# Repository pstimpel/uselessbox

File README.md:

# uselessbox
Just another useless box

3D printed useless box or so called useless machines. Arduino driven. Features 4 servos and a gesture/proximity sensor. Contains a 16 LED neopixel ring. All parts are easy to source. 

## Video in Action
https://www.youtube.com/watch?v=pDcApzEbbxg

## List of parts, sources (no affiliate links)
1x Arduino Nano V3 5V

1x Gesture/proximity sensor, 5V (!) similar to https://www.distrelec.de/de/naeherungs-licht-rgb-und-gestensensor-apds9960-5v-adafruit-3595/p/30139163

1x switch, similar to https://www.amazon.de/gp/product/B07MY2WVQ3/

1x jack similar to https://www.amazon.de/gp/product/B009PH1J5Y/

1x power adaptor similar to https://www.amazon.de/gp/product/B07HSPT57Y

4x servo motors, similar to https://www.amazon.de/gp/product/B06XQD18QN

cables, solder stuff

22x M3*10 scews

5x M3*8 screws

2x M3*20 screws

1x Neopixel 16 LED ring similar to https://www.distrelec.de/de/neopixel-ring-mit-16-rgb-leds-adafruit-1463-neopixel/p/30091142

1x resistor 1/4W 260 Ohm

1x resistor 1/4W 10 kOhm

20x 2.54mm pin headers

2x 5mm 2pol screw terminals

some steering servo push wire, 0.6mm will do. You need about 10 cm.

some double sided tape

optional: stuff to create PCBs

## Instructions
Optional: create your PCB

Just 3d print the parts, each part one time. I printed the "OK fingers" in 0.1mm, and all other stuff in 0.25mm. I used cubic infill, 2 shells, and 3 shells on bottom and top. I did not use any support except for the LED housing. I was using PLA from https://dasfilament.de

Mount one servo to the back part. The axis on top is showing to the outside. Add the lid servo arm. Mount the lid to the back using M3*20 screws. Now use the steering servo push wire. Make sure your servo is at center position when doing that. Make the wire as long as you need it so the lid and back are located rectangular.

Mount the back to the bottom, using 4 M3*10 screws. 

Mount the usb door using the usb door frame, to the the front. Mount the front to the bottom using 4 M3*10 screws.

Mount the jack to the bottom rear and lock it using the "Buchsenhalter" (sorry, forgot to translate it) to the bottom. Use 2 M3*8 screws.

Solder 5 cables to the gesture sensor board, but do not use the pins for this breakout board. If you have, use some old servo cable or anything similar that would match to pins at your main board if you use any. If there are no pins, you will have to solder the wires to the main board later. Make the cables around 15cm long. Mount the sensor board to the top, using the Sensorlock and 2 M3*8 screws.

Solder 2 cables to your switch. Mount the switch to the top. The "on position" of the switch has to show away from the sensor board. Make these cables around 15cm long.

Solder 3 more cables to your neopixel ring (ground, V+, data in). Make these cables 15 cm long, and use again some old servo cables or other cables matching pins. Add the neopixel ring to the housing, and close it using the LED cover. Btw, print this in transparent filament, if you have. Nice light effects are waiting for you. Lock the housing and the cover by another M3*8 screw. The neopixel ring points towards the cover with its LEDs. Mount the LED housing on top of your top part, and lock it using some M3*10 screws. The LED point towards the front. Moint the "flag arm" to one servo, and this servo to the top part. If you look from behind, the axis points to you and to the left. You can add some white label to the flag holder, to create a small flag. Mount the top to the front using another 4 M3*10 screws.

Mount the finger to one servo, do not lock it up yet. Mount the servo to the right housing part, axis to the right. Mount the right housing to the already mounted parts, mount it on the right side when you look from behind! Use 5 M3*10 screws.

OK, we enter the finish line, slowly...

Mount the 4th servo to the "left" part. Axis point to the front, but downwards. Connect OK fingers and "assholearm" together using another M3*10 screw. Mount the whole arm to the servo. DO NOT CLOSE THE HOUSING YET!

Connect all wires (servos, LED, switch, jack, gesture sensor) to your PCB. Take care for not short cutting anything. Use double sided tape and mount your PCB in a way you can reach the USB of te arduino throught the "usb door" at the front of your housing. Make sure again you do not block any servo movement by cables.

It is time to connect the power adaptor. If nothing smokes, you got your solder job the right way.

Make sure the switch on top of your new toy is in Off position, pointing to the front. Connect USB and your PC. Fire up your Arduino IDE, load the sketch and push it to the Arduino. Maybe you need to activate libraries for servos, or FastLED or the gesture sensor. Just follow the instruction of these vendors.

After the reboot, the LED should light up in blue and kind of glow...if you put your finger on the sensor, it should glow red, brightness depending on how close your finger is to the sensor.

At the same time, all your servos were "reset". You can now tighten all the screws of the servo arms connecting to the servo heads.

Servo for Lid: in reset position the LID should be closed

Servo for Flag: in reset position the flag arm should be horizontal, but below the edge of the top.

Servo for OKFinger/Asshole: The door should be closed, the fingers hidden.

Servo for Finger: Tricky one. Push the switch backwards and watch your finger if it makes it way to the switch. Idealy, it should turn the switch off. Just adjust until this happens. Hint: give a little extra push, just about 2-3 mm. Finally, tighten the screw.

OK, if all mechanics are working as expected, your useless machine should work as expected. You can now close the housing, using the last 5 M3*10 screws.

## What does it do?
Basically, the Arduino will cycle trough different ways the servos work. To start the machine, just push the switch to on. The main task of this machine is to push the switch into its off position.

Step 1: open lid, push switch off

Step 2: open lid very harsh, push switch off. After that the lid will open depending on how close your finger is to the sensor.

Step 3: open lid again, push switch off

Step 4: open lid, waving white flag, close the lid. Open the lid, push off the switch, close the lid.

Step 5: show the OK finger / asshole finger (as you prefer), then open the lid, push the switch, close the lid.

Of course you are invited to extent the possible action, color codes and so on. Just make sure to not use "delay()" too heavy, since this will interrupt the glowing of the LED.

## Frequently asked questions
### Why do you enable and disable the servos that much?
I found my servos to be really cheap ones. They interfere with each other. Disabling the servos I do not need for the moment solved this. However, in the video you can see the servos "choking". If you can, buy quality servos.

## Credits
The "OK finger" was remixed out of https://www.thingiverse.com/thing:3370059 by tdkahn1978 .

## Crosslinks

Repo
https://github.com/pstimpel/uselessbox

Thingiverse
https://www.thingiverse.com/thing:3901482

Prusaprinters
https://www.prusaprinters.org/prints/6042-another-useless-box

Youtube
https://www.youtube.com/watch?v=pDcApzEbbxg

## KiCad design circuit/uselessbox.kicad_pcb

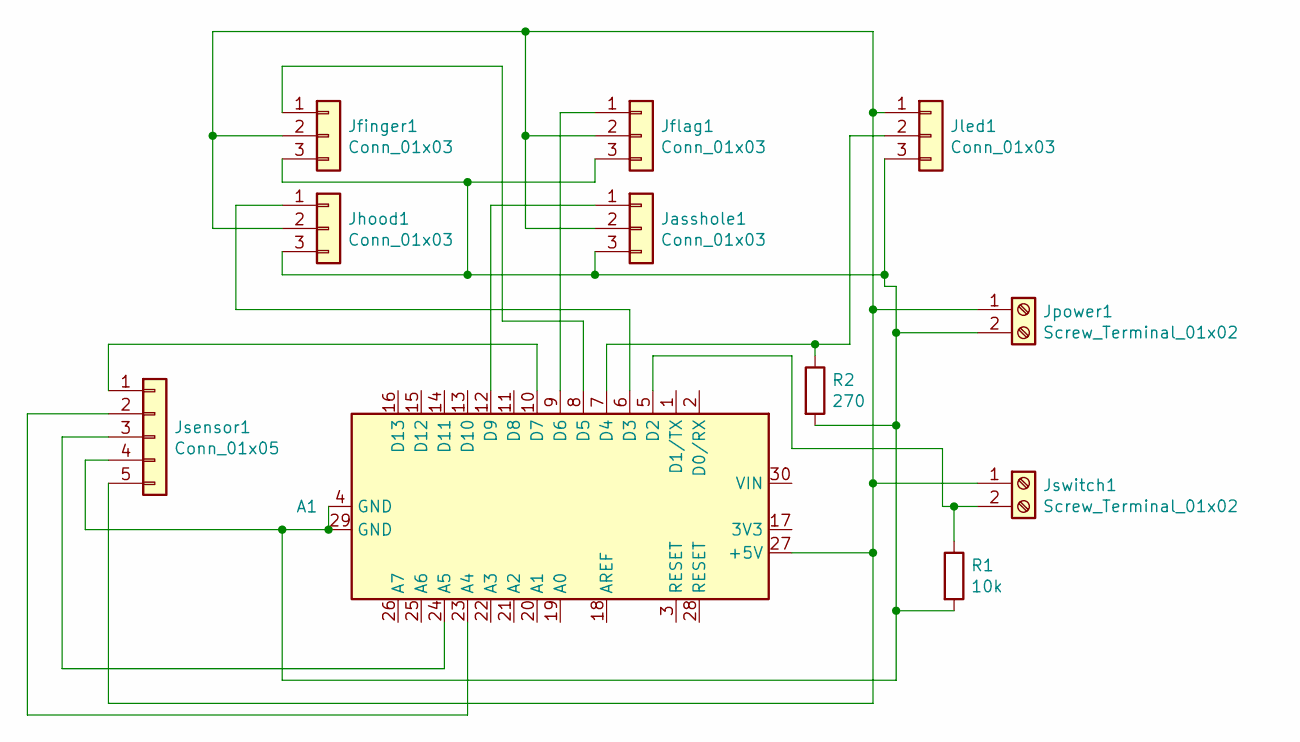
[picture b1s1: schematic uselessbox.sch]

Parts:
A1: n; Arduino_Nano
Jasshole1: Conn_01x03; PinHeader_1x03_P2.54mm_Vertical
Jfinger1: Conn_01x03; PinHeader_1x03_P2.54mm_Vertical
Jflag1: Conn_01x03; PinHeader_1x03_P2.54mm_Vertical
Jhood1: Conn_01x03; PinHeader_1x03_P2.54mm_Vertical
Jled1: Conn_01x03; PinHeader_1x03_P2.54mm_Vertical
Jpower1: Screw_Terminal_01x02; TerminalBlock_Altech_AK300-2_P5.00mm
Jsensor1: Conn_01x05; PinHeader_1x05_P2.54mm_Vertical
Jswitch1: Screw_Terminal_01x02; TerminalBlock_Altech_AK300-2_P5.00mm
R1: 10k; R_Axial_DIN0204_L3.6mm_D1.6mm_P7.62mm_Horizontal
R2: 270; R_Axial_DIN0204_L3.6mm_D1.6mm_P7.62mm_Horizontal

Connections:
unnamed: A1.5 (D2), Jswitch1.2, R1.1
unnamed: A1.6 (D3), Jhood1.1
unnamed: A1.7 (D4), Jled1.2, R2.1
unnamed: A1.8 (D5), Jfinger1.1
unnamed: A1.9 (D6), Jflag1.1
unnamed: A1.10 (D7), Jsensor1.1
unnamed: A1.12 (D9), Jasshole1.1
unnamed: A1.23 (A4), Jsensor1.2
unnamed: A1.24 (A5), Jsensor1.3
unnamed: A1.27 (+5V), Jasshole1.2, Jfinger1.2, Jflag1.2, Jhood1.2, Jled1.1, Jpower1.1, Jsensor1.5, Jswitch1.1
unnamed: A1.4 (GND), A1.29 (GND), Jasshole1.3, Jfinger1.3, Jflag1.3, Jhood1.3, Jled1.3, Jpower1.2, Jsensor1.4, R1.2, R2.2

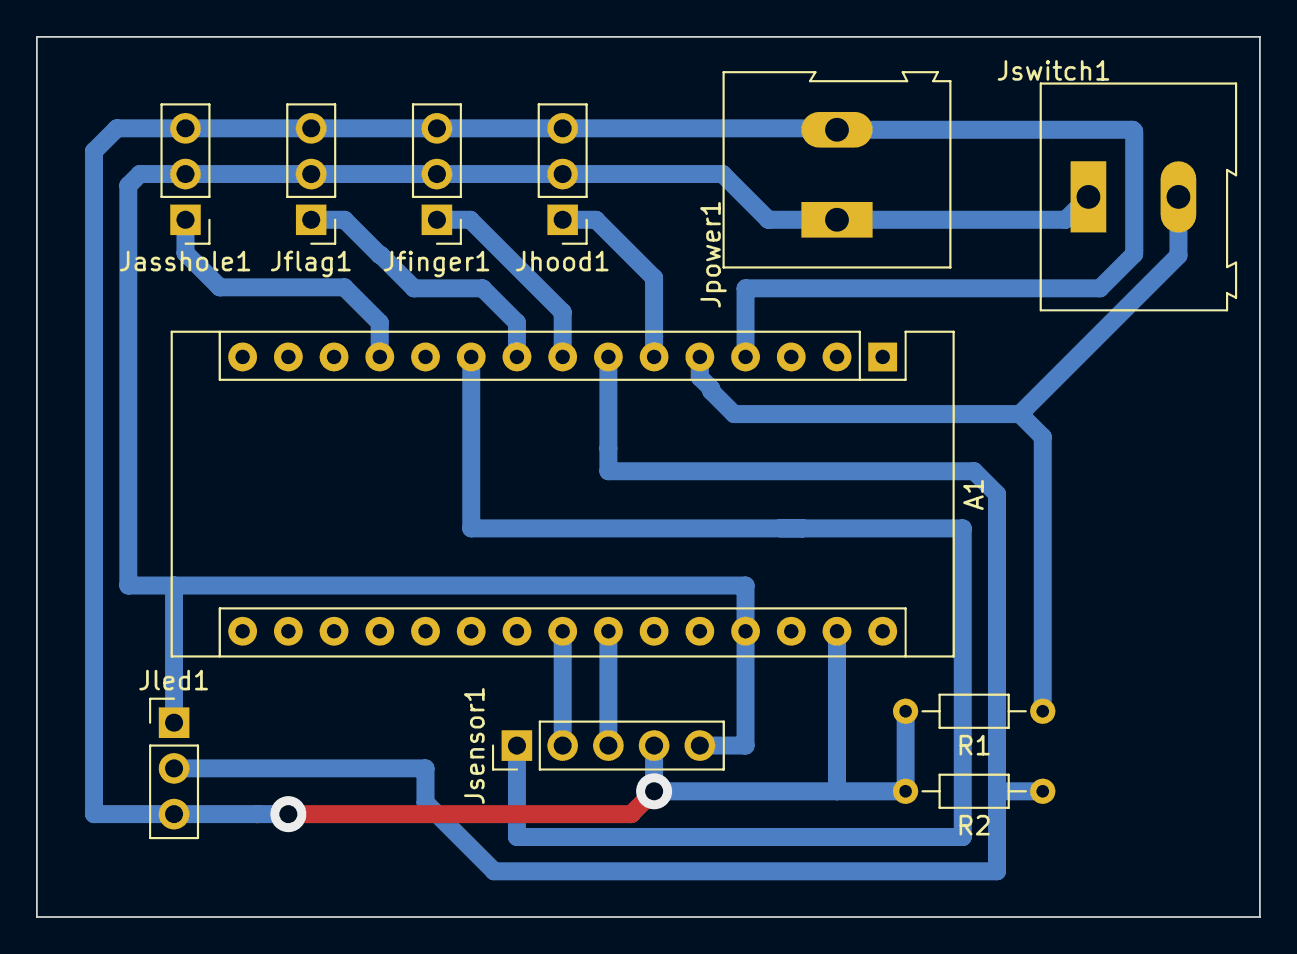
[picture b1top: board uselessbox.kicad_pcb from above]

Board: 2 copper layers, 67.9 x 48.9 mm, 11 parts (0 on the bottom side), 11 nets.

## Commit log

2019-10-06 Create LICENSE
2019-10-06 Update LICENSE
2019-10-06 Arduino stuff and KICAD project for circuit and pcb
2019-10-06 STL files and readme
2019-10-06 Typos in readme
2019-10-06 Crosslinking
